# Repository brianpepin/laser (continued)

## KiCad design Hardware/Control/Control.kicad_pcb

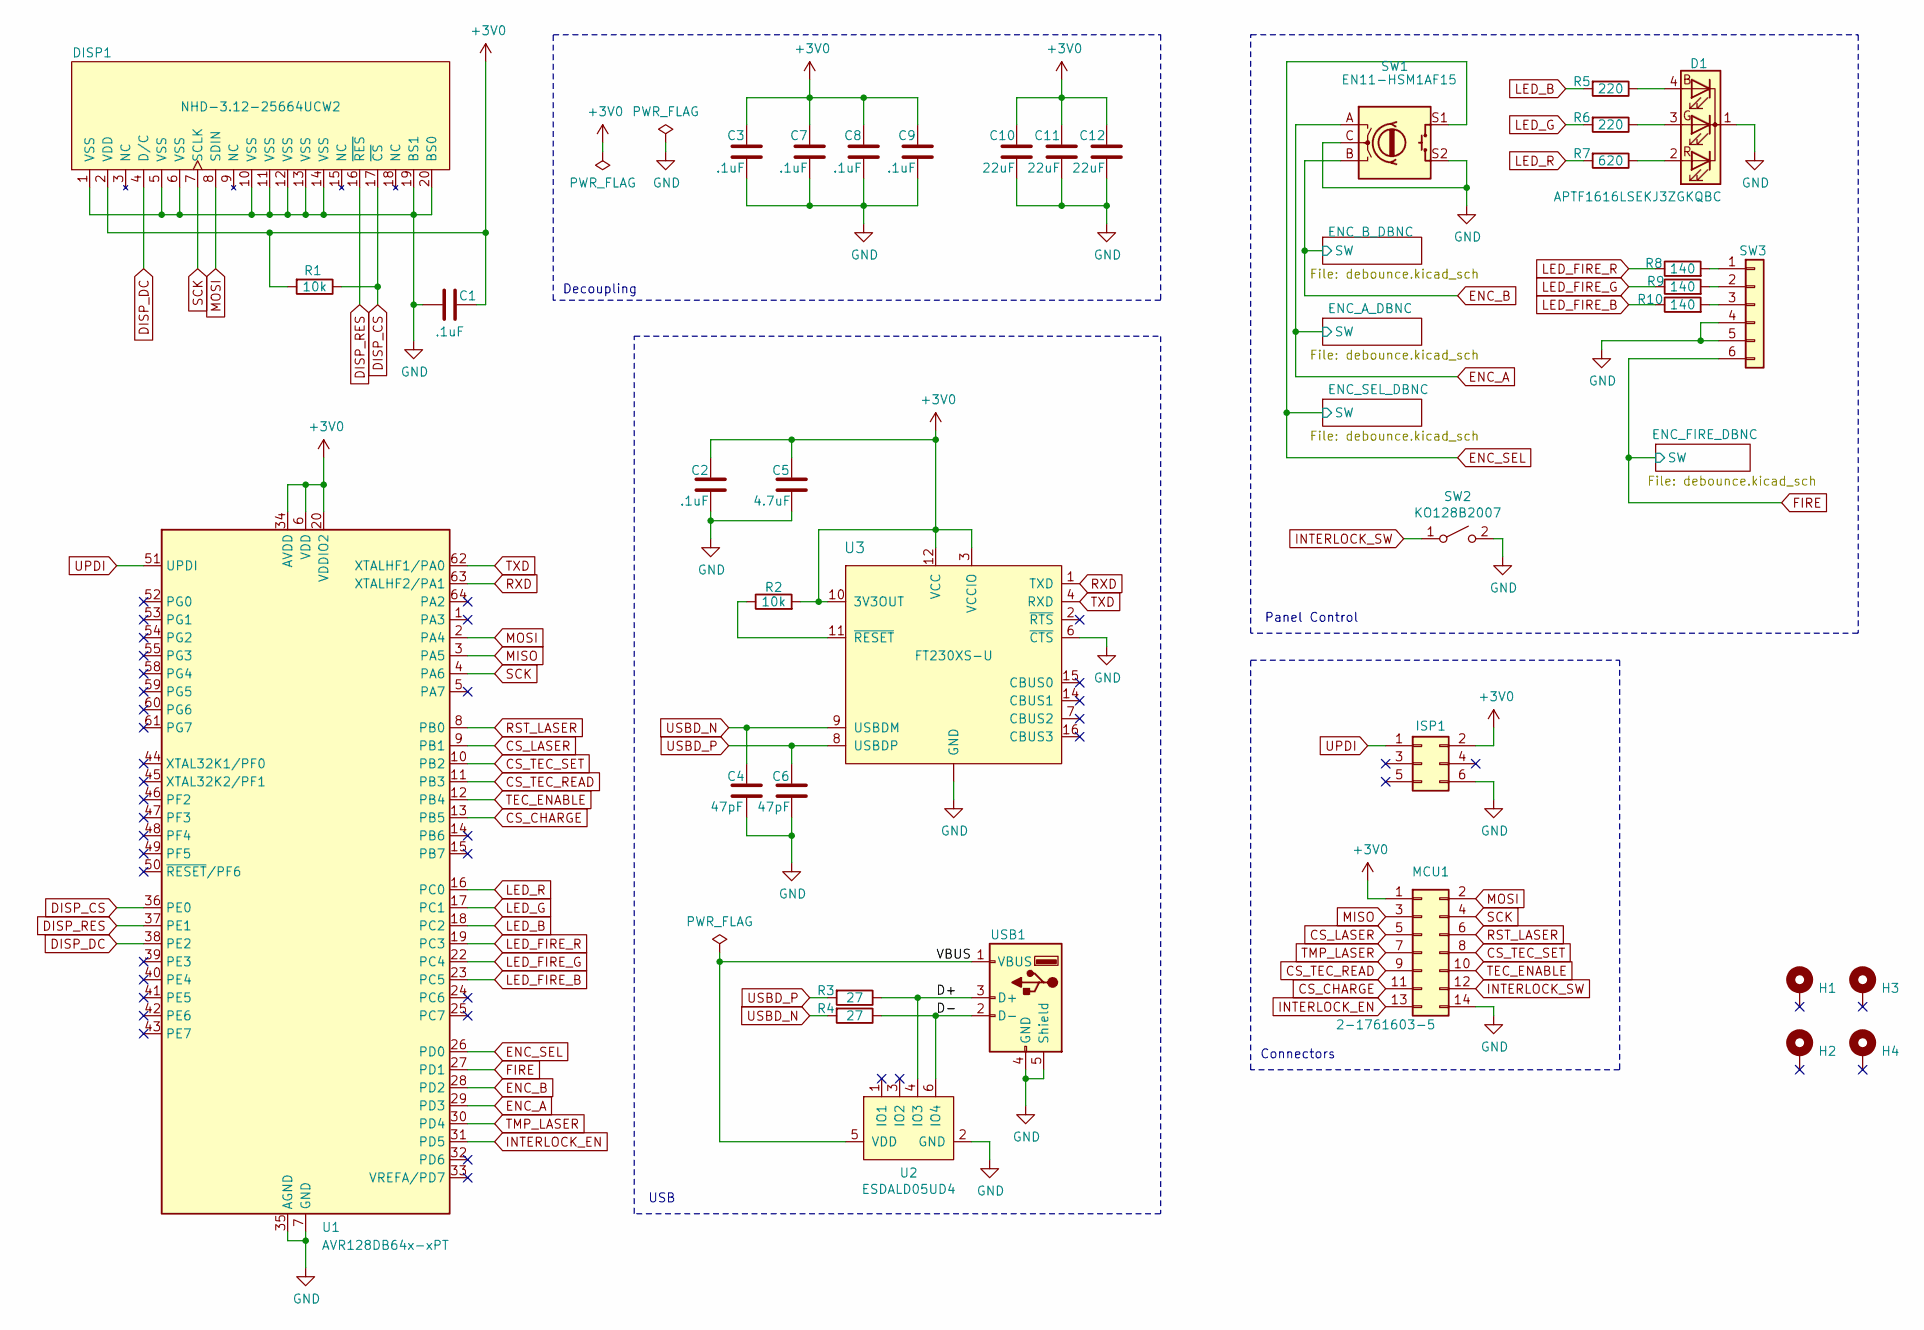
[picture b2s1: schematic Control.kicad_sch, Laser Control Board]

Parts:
C1, C2, C3, C7, C8, C9: .1uF; C_0805_2012Metric
C4, C6: 47pF; C_0805_2012Metric
C5: 4.7uF; C_0805_2012Metric
C10, C11, C12: 22uF; C_1206_3216Metric
D1: APTF1616LSEKJ3ZGKQBC; LED_Kingbright_KRGB_1.6x1.6mm
DISP1: NHD-3.12-25664UCW2; NHD-3.12-25664UC
H1, H2, H3, H4: MountingHole_Pad; MountingHole_3mm_Pad_Via
ISP1: 61200621621; IDC-Header_2x03_P2.54mm_Vertical
MCU1: 2-1761603-5; IDC-Header_2x07_P2.54mm_Vertical
R1, R2: 10k; R_0805_2012Metric
R3, R4: 27; R_0805_2012Metric
R5, R6: 220; R_0805_2012Metric
R7: 620; R_0805_2012Metric
R8, R9, R10: 140; R_0805_2012Metric
SW1: EN11-HSM1AF15; EN11-HSM
SW2: KO128B2007; PinHeader_1x02_P2.54mm_Vertical
SW3: Conn_01x06; PinHeader_1x06_P2.54mm_Vertical
U1: AVR128DB64x-xPT; TQFP-64_10x10mm_P0.5mm
U2: ESDALD05UD4; SOT-23-6
U3: FT230XS-U; SSOP-16_3.9x4.9mm_P0.635mm
USB1: UJ2-A-HR-G-TH; USB-A1HSW6

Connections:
+3V0: C1.2, C2.1, C3.2, C5.1, C7.2, C8.2, C9.2, C10.1, C11.1, C12.1, DISP1.2 (VDD), ISP1.2, MCU1.1, R1.2, R2.2, U1.6 (VDD), U1.20 (VDDIO2), U1.34 (AVDD), U1.56 (VDD), U3.3 (VCCIO), U3.10 (3V3OUT), U3.12 (VCC); also elsewhere on the board
/D+: R3.1, U2.4 (IO3), USB1.3 (D+)
/D-: R4.1, U2.6 (IO4), USB1.2 (D-)
/VBUS: U2.5 (VDD), USB1.1 (VBUS)
CS_CHARGE: MCU1.11, U1.13 (PB5)
CS_LASER: MCU1.5, U1.9 (PB1)
CS_TEC_READ: MCU1.9, U1.11 (PB3)
CS_TEC_SET: MCU1.8, U1.10 (PB2)
DISP_CS: DISP1.17 (~CS), R1.1, U1.36 (PE0)
DISP_DC: DISP1.4 (D/C), U1.38 (PE2)
DISP_RES: DISP1.16 (~RES), U1.37 (PE1)
ENC_A: SW1.A, U1.29 (PD3); also elsewhere on the board
ENC_B: SW1.B, U1.28 (PD2); also elsewhere on the board
ENC_SEL: SW1.S1, U1.26 (PD0); also elsewhere on the board
FIRE: SW3.6, U1.27 (PD1); also elsewhere on the board
GND: C1.1, C2.2, C3.1, C4.2, C5.2, C6.2, C7.1, C8.1, C9.1, C10.2, C11.2, C12.2, D1.1 (K), DISP1.1 (VSS), DISP1.5 (VSS), DISP1.6 (VSS), DISP1.10 (VSS), DISP1.11 (VSS), DISP1.12 (VSS), DISP1.13 (VSS), DISP1.14 (VSS), DISP1.19 (BS1), DISP1.20 (BS0), ISP1.6, MCU1.14, SW1.C, SW1.S2, SW2.2 (B), SW3.4, SW3.5, U1.7 (GND), U1.21 (GND), U1.35 (AGND), U1.57 (GND), U2.2 (GND), U3.5 (GND), U3.6 (~CTS), U3.13 (GND), USB1.4 (GND), USB1.5 (Shield); also elsewhere on the board
INTERLOCK_EN: MCU1.13, U1.31 (PD5)
INTERLOCK_SW: MCU1.12, SW2.1 (A)
LED_B: R5.2, U1.18 (PC2)
LED_FIRE_B: R10.1, U1.23 (PC5)
LED_FIRE_G: R9.1, U1.22 (PC4)
LED_FIRE_R: R8.1, U1.19 (PC3)
LED_G: R6.2, U1.17 (PC1)
LED_R: R7.2, U1.16 (PC0)
MISO: MCU1.3, U1.3 (PA5)
MOSI: DISP1.8 (SDIN), MCU1.2, U1.2 (PA4)
unnamed: D1.4 (BA), R5.1
unnamed: D1.3 (GA), R6.1
unnamed: D1.2 (RA), R7.1
unnamed: R8.2, SW3.1
unnamed: R9.2, SW3.2
unnamed: R10.2, SW3.3
unnamed: R2.1, U3.11 (~RESET)
RST_LASER: MCU1.6, U1.8 (PB0)
RXD: U1.63 (XTALHF2/PA1), U3.1 (TXD)
SCK: DISP1.7 (SCLK), MCU1.4, U1.4 (PA6)
TEC_ENABLE: MCU1.10, U1.12 (PB4)
TMP_LASER: MCU1.7, U1.30 (PD4)
TXD: U1.62 (XTALHF1/PA0), U3.4 (RXD)
UPDI: ISP1.1, U1.51 (UPDI)
USBD_N: C4.1, R4.2, U3.9 (USBDM)
USBD_P: C6.1, R3.2, U3.8 (USBDP)

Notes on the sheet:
USB
Connectors
Panel Control
Decoupling

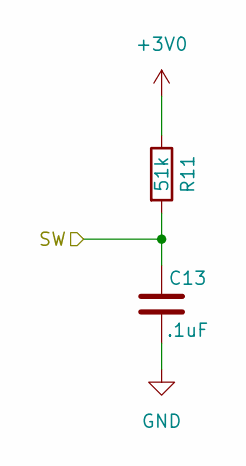
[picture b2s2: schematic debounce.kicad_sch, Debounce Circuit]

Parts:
C13: .1uF; C_0805_2012Metric
R11: 51k; R_0805_2012Metric

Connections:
+3V0: R11.1; also elsewhere on the board
ENC_B: C13.1, R11.2; also elsewhere on the board
GND: C13.2; also elsewhere on the board

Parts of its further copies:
C14, C15, C16: .1uF; C_0805_2012Metric
R12, R13, R14: 51k; R_0805_2012Metric

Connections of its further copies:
+3V0: R12.1, R13.1, R14.1; also elsewhere on the board
ENC_A: C14.1, R12.2; also elsewhere on the board
ENC_SEL: C15.1, R13.2; also elsewhere on the board
FIRE: C16.1, R14.2; also elsewhere on the board
GND: C14.2, C15.2, C16.2; also elsewhere on the board

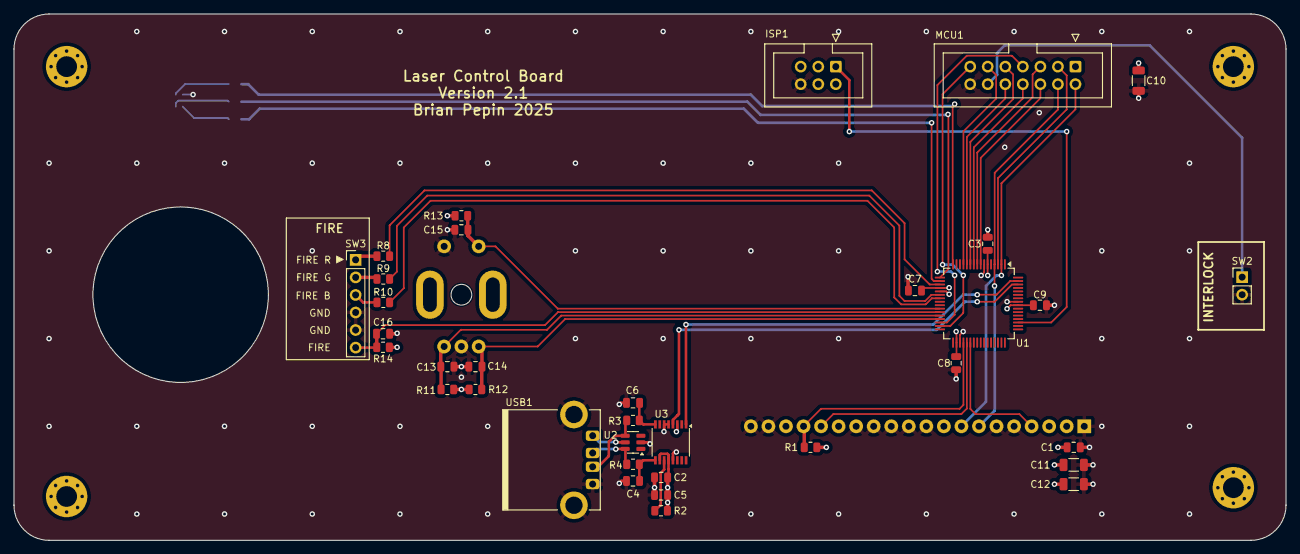
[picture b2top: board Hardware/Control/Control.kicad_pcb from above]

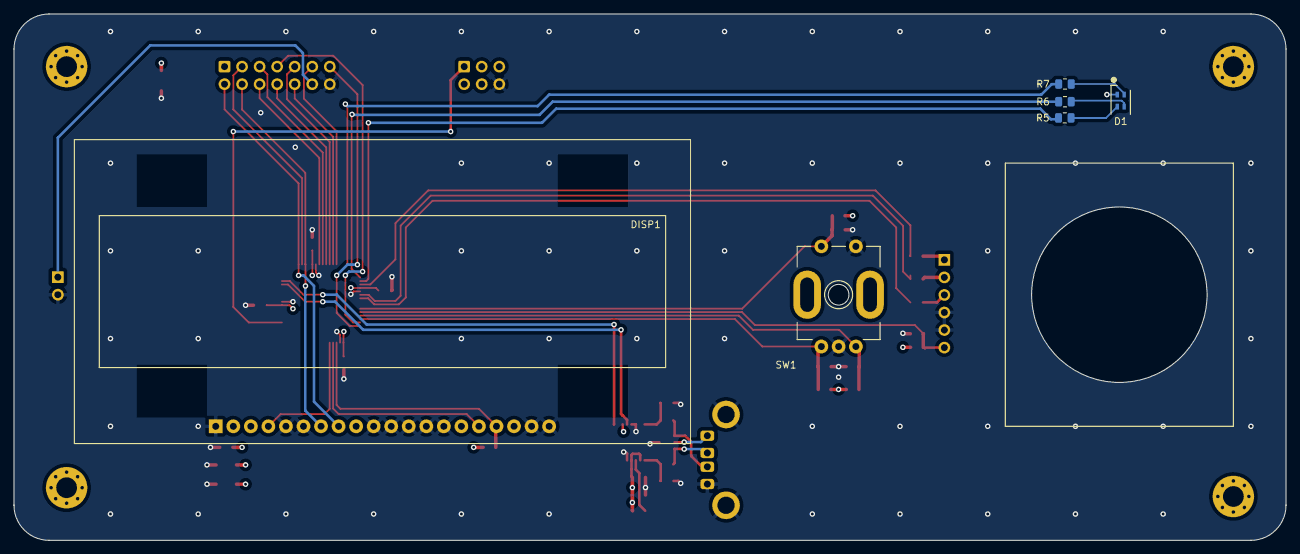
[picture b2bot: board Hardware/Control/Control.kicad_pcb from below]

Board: 4 copper layers, 184.2 x 76.2 mm, 45 parts (6 on the bottom side), 42 nets.

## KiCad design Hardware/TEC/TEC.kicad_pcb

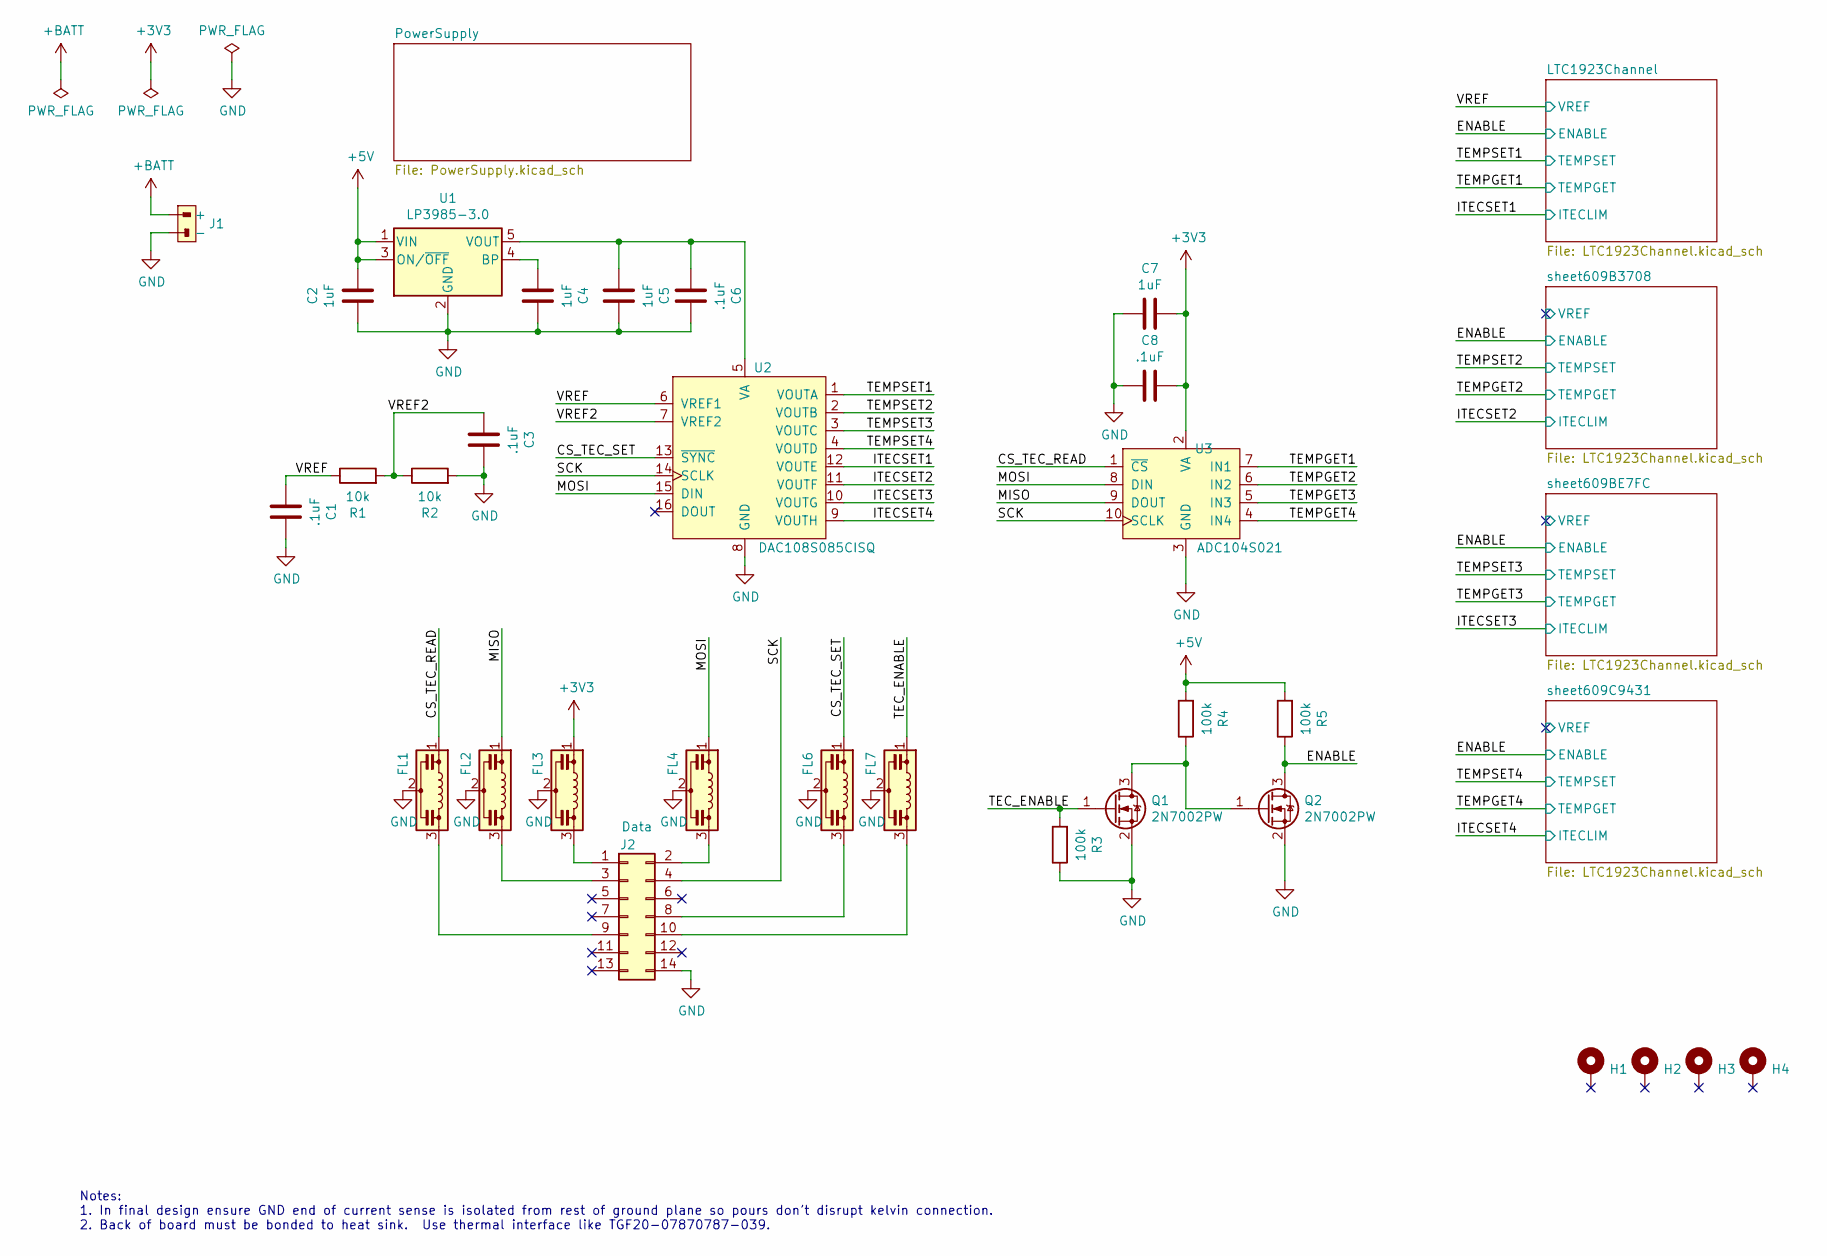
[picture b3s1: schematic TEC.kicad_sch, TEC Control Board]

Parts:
C1, C3, C6, C8: .1uF; C_0805_2012Metric; PartNo VJ0805Y104KXXAT
C2, C4, C5, C7: 1uF; C_0805_2012Metric; PartNo UMF212B7105KGHT
FL1, FL2, FL3, FL4, FL6, FL7: NFL21SP206X1C7D; EMI_805; PartNo NFL21SP206X1C7D
H1, H2, H3, H4: MountingHole_Pad; MountingHole_3mm_Pad_Via
J1: DEANS; Connector_Deans_Male
J2: Data; IDC-Header_2x07_P2.54mm_Horizontal; PartNo 2-1761605-5
Q1, Q2: 2N7002PW; SOT-23; PartNo 2N7002PW,115
R1, R2: 10k; R_0805_2012Metric; PartNo AC0805FR-0710KL
R3, R4, R5: 100k; R_0805_2012Metric; PartNo RC0805FR-07100KL
U1: LP3985-3.0; SOT-23-5; PartNo LP3985IM5X-3.0/NOPB
U2: DAC108S085CISQ; WQFN-16-1EP_4x4mm_P0.5mm_EP2.6x2.6mm_ThermalVias; PartNo DAC108S085CISQ/NOPB
U3: ADC104S021; VSSOP-10_3x3mm_P0.5mm; PartNo ADC104S021CIMMX/NOPB

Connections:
+3V3: C7.1, C8.1, FL3.1, U3.2 (VA)
+5V: C2.1, R4.2, R5.2, U1.1 (VIN), U1.3 (ON/~OFF); also elsewhere on the board
+BATT: J1.+; also elsewhere on the board
/CS_TEC_READ: FL1.1, U3.1 (~CS)
/CS_TEC_SET: FL6.1, U2.13 (~SYNC)
/ENABLE: Q2.3 (D), R5.1; also elsewhere on the board
/ITECSET1: U2.12 (VOUTE); also elsewhere on the board
/ITECSET2: U2.11 (VOUTF); also elsewhere on the board
/ITECSET3: U2.10 (VOUTG); also elsewhere on the board
/ITECSET4: U2.9 (VOUTH); also elsewhere on the board
/MISO: FL2.1, U3.9 (DOUT)
/MOSI: FL4.1, U2.15 (DIN), U3.8 (DIN)
/SCK: J2.4, U2.14 (SCLK), U3.10 (SCLK)
/TEC_ENABLE: FL7.1, Q1.1 (G), R3.2
/TEMPGET1: U3.7 (IN1); also elsewhere on the board
/TEMPGET2: U3.6 (IN2); also elsewhere on the board
/TEMPGET3: U3.5 (IN3); also elsewhere on the board
/TEMPGET4: U3.4 (IN4); also elsewhere on the board
/TEMPSET1: U2.1 (VOUTA); also elsewhere on the board
/TEMPSET2: U2.2 (VOUTB); also elsewhere on the board
/TEMPSET3: U2.3 (VOUTC); also elsewhere on the board
/TEMPSET4: U2.4 (VOUTD); also elsewhere on the board
/VREF: C1.2, R1.1, U2.6 (VREF1); also elsewhere on the board
/VREF2: C3.2, R1.2, R2.1, U2.7 (VREF2)
GND: C1.1, C2.2, C3.1, C4.1, C5.1, C6.1, C7.2, C8.2, FL1.2, FL2.2, FL3.2, FL4.2, FL6.2, FL7.2, J1.-, J2.14, Q1.2 (S), Q2.2 (S), R2.2, R3.1, U1.2 (GND), U2.8 (GND), U2.17 (GND), U3.3 (GND); also elsewhere on the board
unnamed: FL3.3, J2.1
unnamed: FL4.3, J2.2
unnamed: FL2.3, J2.3
unnamed: FL6.3, J2.8
unnamed: FL1.3, J2.9
unnamed: FL7.3, J2.10
unnamed: Q1.3 (D), Q2.1 (G), R4.1
unnamed: C4.2, U1.4 (BP)
unnamed: C5.2, C6.2, U1.5 (VOUT), U2.5 (VA)

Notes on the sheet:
Notes: 1. In final design ensure GND end of current sense is isolated from rest of ground plane so pours don’t disrupt kelvin connection. 2. Back of board must be bonded to heat sink. Use thermal interface like TGF20-07870787-039.

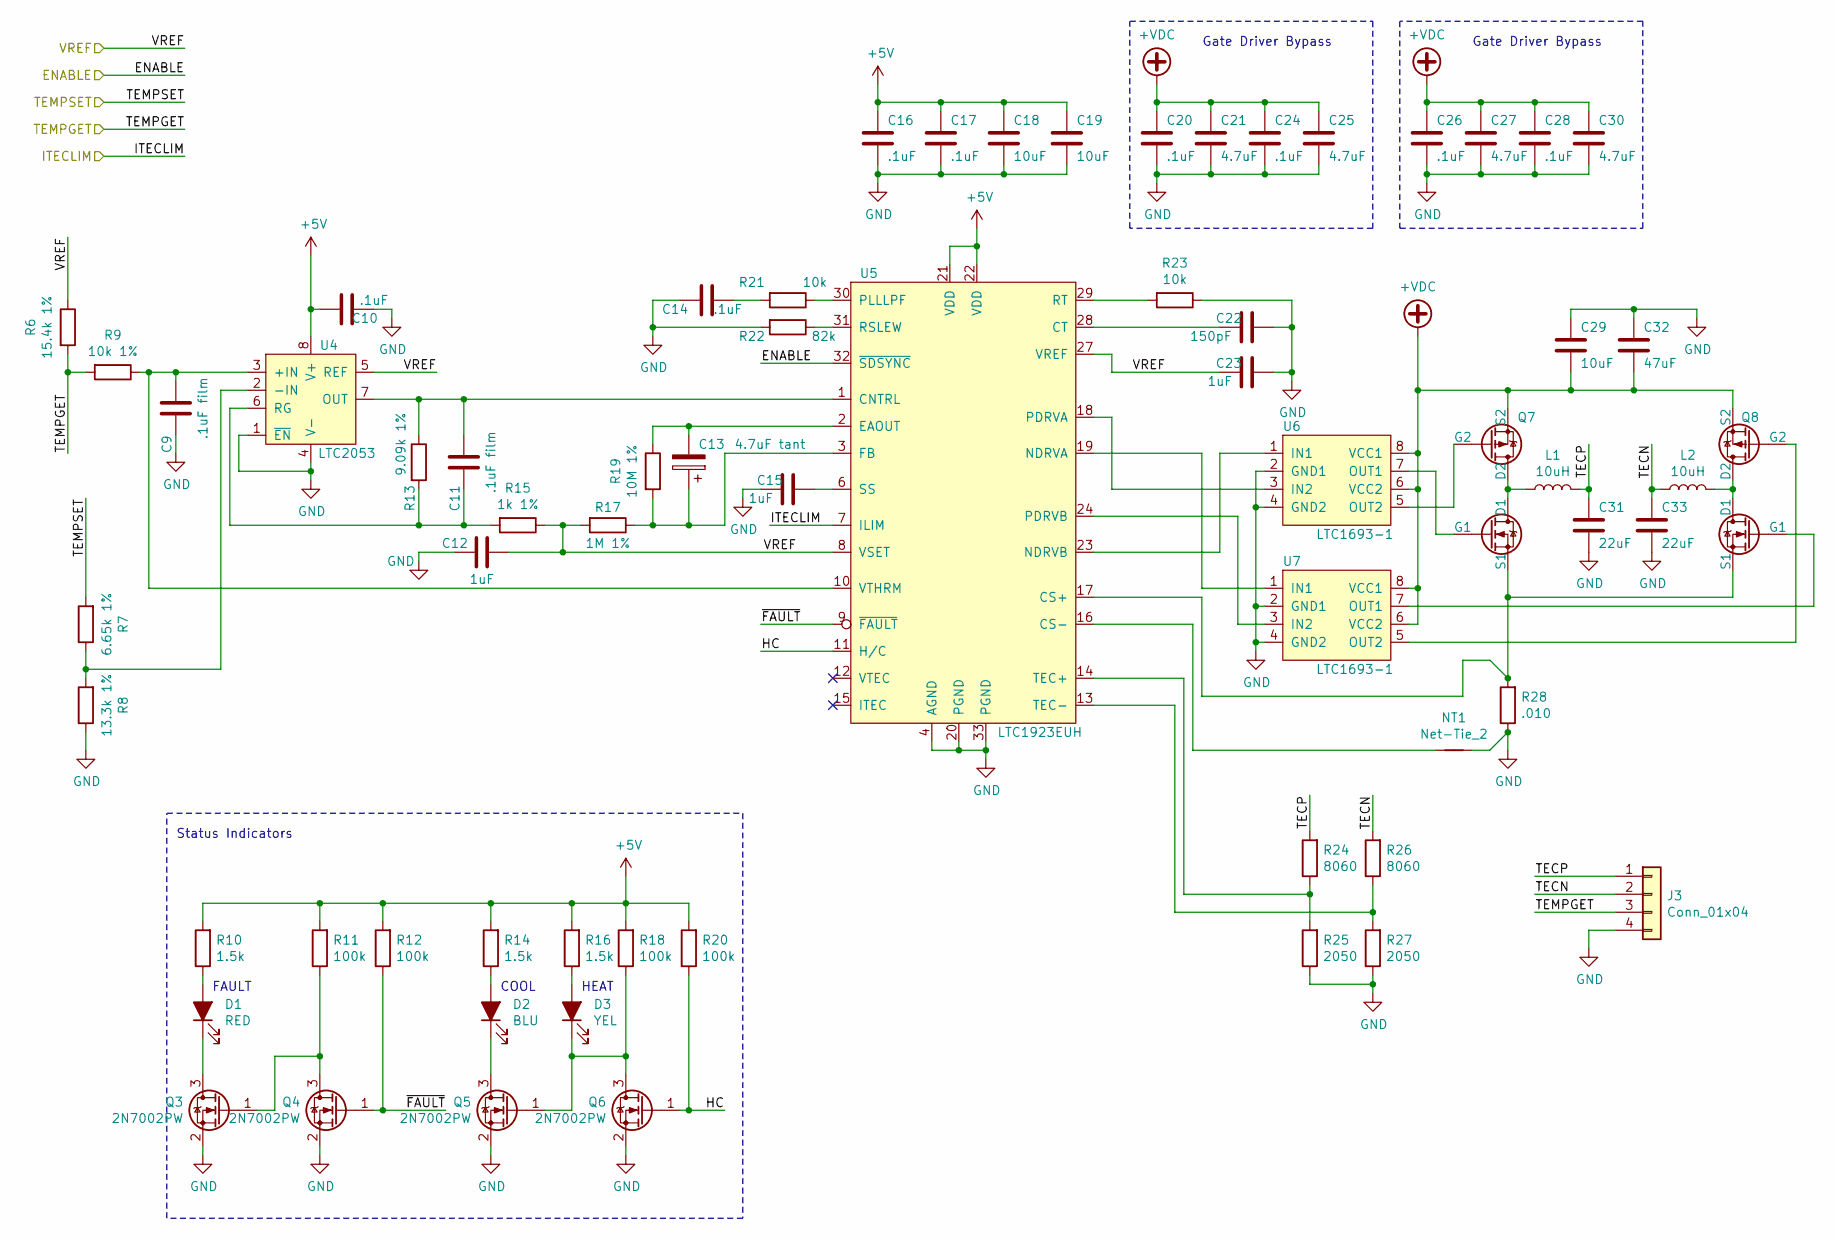
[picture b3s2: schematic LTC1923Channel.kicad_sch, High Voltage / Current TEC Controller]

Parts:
C9, C11: .1uF film; C_0805_2012Metric; PartNo FCA0805C104M-J2
C10, C14, C16, C17, C20, C24, C26, C28: .1uF; C_0805_2012Metric; PartNo VJ0805Y104KXXAT
C12, C15, C23: 1uF; C_0805_2012Metric; PartNo UMF212B7105KGHT
C13: 4.7uF tant; C_0805_2012Metric; PartNo T529P475M025AAE300
C18, C19, C29: 10uF; C_0805_2012Metric; PartNo C2012X7S1E106K125AE
C21, C25, C27, C30: 4.7uF; C_0805_2012Metric; PartNo C0805C475K3RACTU
C22: 150pF; C_0805_2012Metric; PartNo C0805C151J5GACTU
C31, C33: 22uF; C_1206_3216Metric; PartNo 12063D226MAT2A
C32: 47uF; C_1206_3216Metric; PartNo C3216X5R1E476M160AC
D1: RED; LED_0805_2012Metric; PartNo APT2012LSECK/J3-PRV
D2: BLU; LED_0805_2012Metric; PartNo 5973605607F
D3: YEL; LED_0805_2012Metric; PartNo SM0805YCL
J3: Conn_01x04; Molex_Nano-Fit_105313-xx04_1x04_P2.50mm_Horizontal; PartNo 105313-1304
L1, L2: 10uH; L_Pulse_PA4343_2; PartNo PA4343.103ANLT
NT1: Net-Tie_2; NetTie-2_SMD_Pad0.5mm
Q3, Q4, Q5, Q6: 2N7002PW; SOT-23; PartNo 2N7002PW,115
Q7, Q8: SQJ504EP; PowerPAK_SO-8_Dual; PartNo SQJ504EP-T1_GE3
R6: 15.4k 1%; R_0805_2012Metric; PartNo ERJ-6ENF1542V
R7: 6.65k 1%; R_0805_2012Metric; PartNo ERJ-6ENF6651V
R8: 13.3k 1%; R_0805_2012Metric; PartNo CRCW080513K3FKEA
R9: 10k 1%; R_0805_2012Metric; PartNo AC0805FR-0710KL
R10, R14, R16: 1.5k; R_0805_2012Metric; PartNo CR0805-FX-1501ELF
R11, R12, R18, R20: 100k; R_0805_2012Metric; PartNo RC0805FR-07100KL
R13: 9.09k 1%; R_0805_2012Metric; PartNo ERJ-6ENF9091V
R15: 1k 1%; R_0805_2012Metric; PartNo RC0805FR-071KL
R17: 1M 1%; R_0805_2012Metric; PartNo RK73H2ARTTD1004F
R19: 10M 1%; R_0805_2012Metric; PartNo CRCW080510M0FKEAC
R21, R23: 10k; R_0805_2012Metric; PartNo AC0805FR-0710KL
R22: 82k; R_0805_2012Metric; PartNo ERJ-6ENF8202V
R24, R26: 8060; R_0805_2012Metric; PartNo CR0805-FX-8061ELF
R25, R27: 2050; R_0805_2012Metric; PartNo CR0805-FX-2051ELF
R28: .010; R_2010_5025Metric; PartNo TLR2HWDTE10L0F75
U4: LTC2053; MSOP-8_3x3mm_P0.65mm; PartNo LTC2053IMS8#PBF
U5: LTC1923EUH; QFN-32-1EP_5x5mm_P0.5mm_EP3.45x3.45mm_ThermalVias; PartNo LTC1923EUH#PBF
U6, U7: LTC1693-1; SO-8_3.9x4.9mm_P1.27mm; PartNo LTC1693-1IS8#PBF

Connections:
+5V: C10.2, C16.2, C17.2, C18.2, C19.2, R10.2, R11.2, R12.2, R14.2, R16.2, R18.2, R20.2, U4.8 (V+), U5.21 (VDD), U5.22 (VDD); also elsewhere on the board
+VDC: C20.2, C21.2, C24.2, C25.2, C26.2, C27.2, C28.2, C29.1, C30.2, C32.1, Q7.3 (S2), Q8.3 (S2), U6.6 (VCC2), U6.8 (VCC1), U7.6 (VCC2), U7.8 (VCC1); also elsewhere on the board
/ENABLE: U5.32 (~SDSYNC); also elsewhere on the board
/ITECSET1: U5.7 (ILIM); also elsewhere on the board
/LTC1923Channel/HC: Q6.1 (G), R20.1, U5.11 (H/C)
/LTC1923Channel/TECN: C33.2, J3.2, L2.1, R26.2
/LTC1923Channel/TECP: C31.2, J3.1, L1.2, R24.2
/LTC1923Channel/~FAULT: Q4.1 (G), R12.1, U5.9 (~FAULT)
/TEMPGET1: J3.3, R6.2, R9.2; also elsewhere on the board
/TEMPSET1: R7.2; also elsewhere on the board
/VREF: C12.1, C23.1, R6.1, R15.1, R17.2, U4.5 (REF), U5.8 (VSET), U5.27 (VREF); also elsewhere on the board
GND: C9.2, C10.1, C12.2, C14.2, C15.1, C16.1, C17.1, C18.1, C19.1, C20.1, C21.1, C22.2, C23.2, C24.1, C25.1, C26.1, C27.1, C28.1, C29.2, C30.1, C31.1, C32.2, C33.1, J3.4, NT1.2, Q3.2 (S), Q4.2 (S), Q5.2 (S), Q6.2 (S), R8.1, R22.2, R23.1, R25.1, R27.1, R28.1, U4.1 (~EN), U4.4 (V-), U5.4 (AGND), U5.20 (PGND), U5.33 (PGND), U6.2 (GND1), U6.4 (GND2), U7.2 (GND1), U7.4 (GND2); also elsewhere on the board
unnamed: C14.1, R21.2
unnamed: D1.2 (A), R10.1
unnamed: D1.1 (K), Q3.3 (D)
unnamed: D2.2 (A), R14.1
unnamed: D2.1 (K), Q5.3 (D)
unnamed: D3.2 (A), R16.1
unnamed: D3.1 (K), Q5.1 (G), Q6.3 (D), R18.1
unnamed: Q3.1 (G), Q4.3 (D), R11.1
unnamed: L1.1, Q7.5 (D1), Q7.6 (D2)
unnamed: Q7.2 (G1), U6.7 (OUT1)
unnamed: Q7.4 (G2), U6.5 (OUT2)
unnamed: Q7.1 (S1), Q8.1 (S1), R28.2, U5.17 (CS+)
unnamed: L2.2, Q8.5 (D1), Q8.6 (D2)
unnamed: Q8.2 (G1), U7.7 (OUT1)
unnamed: Q8.4 (G2), U7.5 (OUT2)
unnamed: C9.1, R9.1, U4.3 (+IN), U5.10 (VTHRM)
unnamed: R7.1, R8.2, U4.2 (-IN)
unnamed: C11.1, R13.1, U4.7 (OUT), U5.1 (CNTRL)
unnamed: C11.2, R13.2, R15.2, U4.6 (RG)
unnamed: NT1.1, U5.16 (CS-)
unnamed: C22.1, U5.28 (CT)
unnamed: C13.2, R19.1, U5.2 (EAOUT)
unnamed: C13.1, R17.1, R19.2, U5.3 (FB)
unnamed: U5.19 (NDRVA), U7.1 (IN1)
unnamed: U5.23 (NDRVB), U6.1 (IN1)
unnamed: U5.18 (PDRVA), U6.3 (IN2)
unnamed: U5.24 (PDRVB), U7.3 (IN2)
unnamed: R21.1, U5.30 (PLLLPF)
unnamed: R22.1, U5.31 (RSLEW)
unnamed: R23.2, U5.29 (RT)
unnamed: C15.2, U5.6 (SS)
unnamed: R24.1, R25.2, U5.14 (TEC+)
unnamed: R26.1, R27.2, U5.13 (TEC-)

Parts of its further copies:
C36, C38, C61, C63, C86, C88: .1uF film; C_0805_2012Metric; PartNo FCA0805C104M-J2
C37, C41, C43, C44, C47, C51, C53, C55, C62, C66, C68, C69, C72, C76, C78, C80, C87, C91, C93, C94, C97, C101, C103, C105: .1uF; C_0805_2012Metric; PartNo VJ0805Y104KXXAT
C39, C42, C50, C64, C67, C75, C89, C92, C100: 1uF; C_0805_2012Metric; PartNo UMF212B7105KGHT
C40, C65, C90: 4.7uF tant; C_0805_2012Metric; PartNo T529P475M025AAE300
C45, C46, C56, C70, C71, C81, C95, C96, C106: 10uF; C_0805_2012Metric; PartNo C2012X7S1E106K125AE
C48, C52, C54, C57, C73, C77, C79, C82, C98, C102, C104, C107: 4.7uF; C_0805_2012Metric; PartNo C0805C475K3RACTU
C49, C74, C99: 150pF; C_0805_2012Metric; PartNo C0805C151J5GACTU
C58, C60, C83, C85, C108, C110: 22uF; C_1206_3216Metric; PartNo 12063D226MAT2A
C59, C84, C109: 47uF; C_1206_3216Metric; PartNo C3216X5R1E476M160AC
D4, D7, D10: RED; LED_0805_2012Metric; PartNo APT2012LSECK/J3-PRV
D5, D8, D11: BLU; LED_0805_2012Metric; PartNo 5973605607F
D6, D9, D12: YEL; LED_0805_2012Metric; PartNo SM0805YCL
J4, J5, J6: Conn_01x04; Molex_Nano-Fit_105313-xx04_1x04_P2.50mm_Horizontal; PartNo 105313-1304
L3, L4, L5, L6, L7, L8: 10uH; L_Pulse_PA4343_2; PartNo PA4343.103ANLT
NT2, NT3, NT4: Net-Tie_2; NetTie-2_SMD_Pad0.5mm
Q12, Q13, Q14, Q15, Q18, Q19, Q20, Q21, Q24, Q25, Q26, Q27: 2N7002PW; SOT-23; PartNo 2N7002PW,115
Q16, Q17, Q22, Q23, Q28, Q29: SQJ504EP; PowerPAK_SO-8_Dual; PartNo SQJ504EP-T1_GE3
R31, R54, R77: 15.4k 1%; R_0805_2012Metric; PartNo ERJ-6ENF1542V
R32, R55, R78: 6.65k 1%; R_0805_2012Metric; PartNo ERJ-6ENF6651V
R33, R56, R79: 13.3k 1%; R_0805_2012Metric; PartNo CRCW080513K3FKEA
R34, R57, R80: 10k 1%; R_0805_2012Metric; PartNo AC0805FR-0710KL
R35, R39, R41, R58, R62, R64, R81, R85, R87: 1.5k; R_0805_2012Metric; PartNo CR0805-FX-1501ELF
R36, R37, R43, R45, R59, R60, R66, R68, R82, R83, R89, R91: 100k; R_0805_2012Metric; PartNo RC0805FR-07100KL
R38, R61, R84: 9.09k 1%; R_0805_2012Metric; PartNo ERJ-6ENF9091V
R40, R63, R86: 1k 1%; R_0805_2012Metric; PartNo RC0805FR-071KL
R42, R65, R88: 1M 1%; R_0805_2012Metric; PartNo RK73H2ARTTD1004F
R44, R67, R90: 10M 1%; R_0805_2012Metric; PartNo CRCW080510M0FKEAC
R46, R48, R69, R71, R92, R94: 10k; R_0805_2012Metric; PartNo AC0805FR-0710KL
R47, R70, R93: 82k; R_0805_2012Metric; PartNo ERJ-6ENF8202V
R49, R51, R72, R74, R95, R97: 8060; R_0805_2012Metric; PartNo CR0805-FX-8061ELF
R50, R52, R73, R75, R96, R98: 2050; R_0805_2012Metric; PartNo CR0805-FX-2051ELF
R53, R76, R99: .010; R_2010_5025Metric; PartNo TLR2HWDTE10L0F75
U9, U13, U17: LTC2053; MSOP-8_3x3mm_P0.65mm; PartNo LTC2053IMS8#PBF
U10, U14, U18: LTC1923EUH; QFN-32-1EP_5x5mm_P0.5mm_EP3.45x3.45mm_ThermalVias; PartNo LTC1923EUH#PBF
U11, U12, U15, U16, U19, U20: LTC1693-1; SO-8_3.9x4.9mm_P1.27mm; PartNo LTC1693-1IS8#PBF

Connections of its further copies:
+5V: C37.2, C43.2, C44.2, C45.2, C46.2, C62.2, C68.2, C69.2, C70.2, C71.2, C87.2, C93.2, C94.2, C95.2, C96.2, R35.2, R36.2, R37.2, R39.2, R41.2, R43.2, R45.2, R58.2, R59.2, R60.2, R62.2, R64.2, R66.2, R68.2, R81.2, R82.2, R83.2, R85.2, R87.2, R89.2, R91.2, U9.8 (V+), U10.21 (VDD), U10.22 (VDD), U13.8 (V+), U14.21 (VDD), U14.22 (VDD), U17.8 (V+), U18.21 (VDD), U18.22 (VDD); also elsewhere on the board
+VDC: C47.2, C48.2, C51.2, C52.2, C53.2, C54.2, C55.2, C56.1, C57.2, C59.1, C72.2, C73.2, C76.2, C77.2, C78.2, C79.2, C80.2, C81.1, C82.2, C84.1, C97.2, C98.2, C101.2, C102.2, C103.2, C104.2, C105.2, C106.1, C107.2, C109.1, Q16.3 (S2), Q17.3 (S2), Q22.3 (S2), Q23.3 (S2), Q28.3 (S2), Q29.3 (S2), U11.6 (VCC2), U11.8 (VCC1), U12.6 (VCC2), U12.8 (VCC1), U15.6 (VCC2), U15.8 (VCC1), U16.6 (VCC2), U16.8 (VCC1), U19.6 (VCC2), U19.8 (VCC1), U20.6 (VCC2), U20.8 (VCC1); also elsewhere on the board
/ENABLE: U10.32 (~SDSYNC), U14.32 (~SDSYNC), U18.32 (~SDSYNC); also elsewhere on the board
/ITECSET2: U10.7 (ILIM); also elsewhere on the board
/ITECSET3: U14.7 (ILIM); also elsewhere on the board
/ITECSET4: U18.7 (ILIM); also elsewhere on the board
/TEMPGET2: J4.3, R31.2, R34.2; also elsewhere on the board
/TEMPGET3: J5.3, R54.2, R57.2; also elsewhere on the board
/TEMPGET4: J6.3, R77.2, R80.2; also elsewhere on the board
/TEMPSET2: R32.2; also elsewhere on the board
/TEMPSET3: R55.2; also elsewhere on the board
/TEMPSET4: R78.2; also elsewhere on the board
/sheet609B3708/HC: Q15.1 (G), R45.1, U10.11 (H/C)
/sheet609B3708/TECN: C60.2, J4.2, L4.1, R51.2
/sheet609B3708/TECP: C58.2, J4.1, L3.2, R49.2
/sheet609B3708/VREF: C39.1, C50.1, R31.1, R40.1, R42.2, U9.5 (REF), U10.8 (VSET), U10.27 (VREF)
/sheet609B3708/~FAULT: Q13.1 (G), R37.1, U10.9 (~FAULT)
/sheet609BE7FC/HC: Q21.1 (G), R68.1, U14.11 (H/C)
/sheet609BE7FC/TECN: C85.2, J5.2, L6.1, R74.2
/sheet609BE7FC/TECP: C83.2, J5.1, L5.2, R72.2
/sheet609BE7FC/VREF: C64.1, C75.1, R54.1, R63.1, R65.2, U13.5 (REF), U14.8 (VSET), U14.27 (VREF)
/sheet609BE7FC/~FAULT: Q19.1 (G), R60.1, U14.9 (~FAULT)
/sheet609C9431/HC: Q27.1 (G), R91.1, U18.11 (H/C)
/sheet609C9431/TECN: C110.2, J6.2, L8.1, R97.2
/sheet609C9431/TECP: C108.2, J6.1, L7.2, R95.2
/sheet609C9431/VREF: C89.1, C100.1, R77.1, R86.1, R88.2, U17.5 (REF), U18.8 (VSET), U18.27 (VREF)
/sheet609C9431/~FAULT: Q25.1 (G), R83.1, U18.9 (~FAULT)
GND: C36.2, C37.1, C39.2, C41.2, C42.1, C43.1, C44.1, C45.1, C46.1, C47.1, C48.1, C49.2, C50.2, C51.1, C52.1, C53.1, C54.1, C55.1, C56.2, C57.1, C58.1, C59.2, C60.1, C61.2, C62.1, C64.2, C66.2, C67.1, C68.1, C69.1, C70.1, C71.1, C72.1, C73.1, C74.2, C75.2, C76.1, C77.1, C78.1, C79.1, C80.1, C81.2, C82.1, C83.1, C84.2, C85.1, C86.2, C87.1, C89.2, C91.2, C92.1, C93.1, C94.1, C95.1, C96.1, C97.1, C98.1, C99.2, C100.2, C101.1, C102.1, C103.1, C104.1, C105.1, C106.2, C107.1, C108.1, C109.2, C110.1, J4.4, J5.4, J6.4, NT2.2, NT3.2, NT4.2, Q12.2 (S), Q13.2 (S), Q14.2 (S), Q15.2 (S), Q18.2 (S), Q19.2 (S), Q20.2 (S), Q21.2 (S), Q24.2 (S), Q25.2 (S), Q26.2 (S), Q27.2 (S), R33.1, R47.2, R48.1, R50.1, R52.1, R53.1, R56.1, R70.2, R71.1, R73.1, R75.1, R76.1, R79.1, R93.2, R94.1, R96.1, R98.1, R99.1, U9.1 (~EN), U9.4 (V-), U10.4 (AGND), U10.20 (PGND), U10.33 (PGND), U11.2 (GND1), U11.4 (GND2), U12.2 (GND1), U12.4 (GND2), U13.1 (~EN), U13.4 (V-), U14.4 (AGND), U14.20 (PGND), U14.33 (PGND), U15.2 (GND1), U15.4 (GND2), U16.2 (GND1), U16.4 (GND2), U17.1 (~EN), U17.4 (V-), U18.4 (AGND), U18.20 (PGND), U18.33 (PGND), U19.2 (GND1), U19.4 (GND2), U20.2 (GND1), U20.4 (GND2); also elsewhere on the board
unnamed: C41.1, R46.2
unnamed: C66.1, R69.2
unnamed: C91.1, R92.2
unnamed: D4.2 (A), R35.1
unnamed: D4.1 (K), Q12.3 (D)
unnamed: D5.2 (A), R39.1
unnamed: D5.1 (K), Q14.3 (D)
unnamed: D6.2 (A), R41.1
unnamed: D6.1 (K), Q14.1 (G), Q15.3 (D), R43.1
unnamed: D7.2 (A), R58.1
unnamed: D7.1 (K), Q18.3 (D)
unnamed: D8.2 (A), R62.1
unnamed: D8.1 (K), Q20.3 (D)
unnamed: D9.2 (A), R64.1
unnamed: D9.1 (K), Q20.1 (G), Q21.3 (D), R66.1
unnamed: D10.2 (A), R81.1
unnamed: D10.1 (K), Q24.3 (D)
unnamed: D11.2 (A), R85.1
unnamed: D11.1 (K), Q26.3 (D)
unnamed: D12.2 (A), R87.1
unnamed: D12.1 (K), Q26.1 (G), Q27.3 (D), R89.1
unnamed: Q12.1 (G), Q13.3 (D), R36.1
unnamed: L3.1, Q16.5 (D1), Q16.6 (D2)
unnamed: Q16.2 (G1), U11.7 (OUT1)
unnamed: Q16.4 (G2), U11.5 (OUT2)
unnamed: Q16.1 (S1), Q17.1 (S1), R53.2, U10.17 (CS+)
unnamed: L4.2, Q17.5 (D1), Q17.6 (D2)
unnamed: Q17.2 (G1), U12.7 (OUT1)
unnamed: Q17.4 (G2), U12.5 (OUT2)
unnamed: Q18.1 (G), Q19.3 (D), R59.1
unnamed: L5.1, Q22.5 (D1), Q22.6 (D2)
unnamed: Q22.2 (G1), U15.7 (OUT1)
unnamed: Q22.4 (G2), U15.5 (OUT2)
unnamed: Q22.1 (S1), Q23.1 (S1), R76.2, U14.17 (CS+)
unnamed: L6.2, Q23.5 (D1), Q23.6 (D2)
unnamed: Q23.2 (G1), U16.7 (OUT1)
unnamed: Q23.4 (G2), U16.5 (OUT2)
unnamed: Q24.1 (G), Q25.3 (D), R82.1
unnamed: L7.1, Q28.5 (D1), Q28.6 (D2)
unnamed: Q28.2 (G1), U19.7 (OUT1)
unnamed: Q28.4 (G2), U19.5 (OUT2)
unnamed: Q28.1 (S1), Q29.1 (S1), R99.2, U18.17 (CS+)
unnamed: L8.2, Q29.5 (D1), Q29.6 (D2)
unnamed: Q29.2 (G1), U20.7 (OUT1)
unnamed: Q29.4 (G2), U20.5 (OUT2)
unnamed: R32.1, R33.2, U9.2 (-IN)
unnamed: C38.2, R38.2, R40.2, U9.6 (RG)
unnamed: C38.1, R38.1, U9.7 (OUT), U10.1 (CNTRL)
unnamed: NT2.1, U10.16 (CS-)
unnamed: C49.1, U10.28 (CT)
unnamed: C40.2, R44.1, U10.2 (EAOUT)
unnamed: C40.1, R42.1, R44.2, U10.3 (FB)
unnamed: U10.19 (NDRVA), U12.1 (IN1)
unnamed: U10.23 (NDRVB), U11.1 (IN1)
unnamed: U10.18 (PDRVA), U11.3 (IN2)
unnamed: U10.24 (PDRVB), U12.3 (IN2)
unnamed: R46.1, U10.30 (PLLLPF)
unnamed: R47.1, U10.31 (RSLEW)
unnamed: R48.2, U10.29 (RT)
unnamed: C42.2, U10.6 (SS)
unnamed: R49.1, R50.2, U10.14 (TEC+)
unnamed: R51.1, R52.2, U10.13 (TEC-)
unnamed: C36.1, R34.1, U9.3 (+IN), U10.10 (VTHRM)
unnamed: C61.1, R57.1, U13.3 (+IN), U14.10 (VTHRM)
unnamed: R55.1, R56.2, U13.2 (-IN)
unnamed: C63.1, R61.1, U13.7 (OUT), U14.1 (CNTRL)
unnamed: C63.2, R61.2, R63.2, U13.6 (RG)
unnamed: NT3.1, U14.16 (CS-)
unnamed: C74.1, U14.28 (CT)
unnamed: C65.2, R67.1, U14.2 (EAOUT)
unnamed: C65.1, R65.1, R67.2, U14.3 (FB)
unnamed: U14.19 (NDRVA), U16.1 (IN1)
unnamed: U14.23 (NDRVB), U15.1 (IN1)
unnamed: U14.18 (PDRVA), U15.3 (IN2)
unnamed: U14.24 (PDRVB), U16.3 (IN2)
unnamed: R69.1, U14.30 (PLLLPF)
unnamed: R70.1, U14.31 (RSLEW)
unnamed: R71.2, U14.29 (RT)
unnamed: C67.2, U14.6 (SS)
unnamed: R72.1, R73.2, U14.14 (TEC+)
unnamed: R74.1, R75.2, U14.13 (TEC-)
unnamed: C86.1, R80.1, U17.3 (+IN), U18.10 (VTHRM)
unnamed: R78.1, R79.2, U17.2 (-IN)
unnamed: C88.1, R84.1, U17.7 (OUT), U18.1 (CNTRL)
unnamed: C88.2, R84.2, R86.2, U17.6 (RG)
unnamed: NT4.1, U18.16 (CS-)
unnamed: C99.1, U18.28 (CT)
unnamed: C90.2, R90.1, U18.2 (EAOUT)
unnamed: C90.1, R88.1, R90.2, U18.3 (FB)
unnamed: U18.19 (NDRVA), U20.1 (IN1)
unnamed: U18.23 (NDRVB), U19.1 (IN1)
unnamed: U18.18 (PDRVA), U19.3 (IN2)
unnamed: U18.24 (PDRVB), U20.3 (IN2)
unnamed: R92.1, U18.30 (PLLLPF)
unnamed: R93.1, U18.31 (RSLEW)
unnamed: R94.2, U18.29 (RT)
unnamed: C92.2, U18.6 (SS)
unnamed: R95.1, R96.2, U18.14 (TEC+)
unnamed: R97.1, R98.2, U18.13 (TEC-)

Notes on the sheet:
Gate Driver Bypass
COOL
HEAT
Status Indicators
FAULT

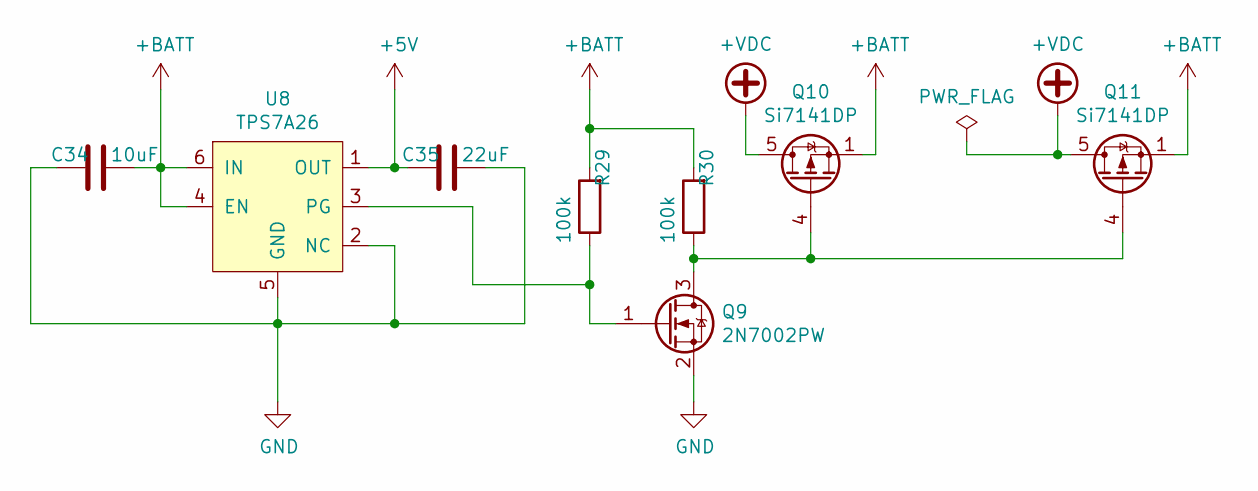
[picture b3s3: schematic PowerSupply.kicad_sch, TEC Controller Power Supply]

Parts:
C34: 10uF; C_0805_2012Metric; PartNo C2012X7S1E106K125AE
C35: 22uF; C_1206_3216Metric; PartNo 12063D226MAT2A
Q9: 2N7002PW; SOT-23; PartNo 2N7002PW,115
Q10, Q11: Si7141DP; PowerPAK_SO-8_Single; PartNo SI7141DP-T1-GE3
R29, R30: 100k; R_0805_2012Metric; PartNo RC0805FR-07100KL
U8: TPS7A26; WSON-6-1EP_2x2mm_P0.65mm_EP1x1.6mm_ThermalVias; PartNo TPS7A2650DRVR

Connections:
+5V: C35.2, U8.1 (OUT); also elsewhere on the board
+BATT: C34.1, Q10.1 (S), Q10.2 (S), Q10.3 (S), Q11.1 (S), Q11.2 (S), Q11.3 (S), R29.2, R30.2, U8.4 (EN), U8.6 (IN); also elsewhere on the board
+VDC: Q10.5 (D), Q11.5 (D); also elsewhere on the board
GND: C34.2, C35.1, Q9.2 (S), U8.2 (NC), U8.5 (GND), U8.7 (GND); also elsewhere on the board
unnamed: Q9.1 (G), R29.1, U8.3 (PG)
unnamed: Q9.3 (D), Q10.4 (G), Q11.4 (G), R30.1

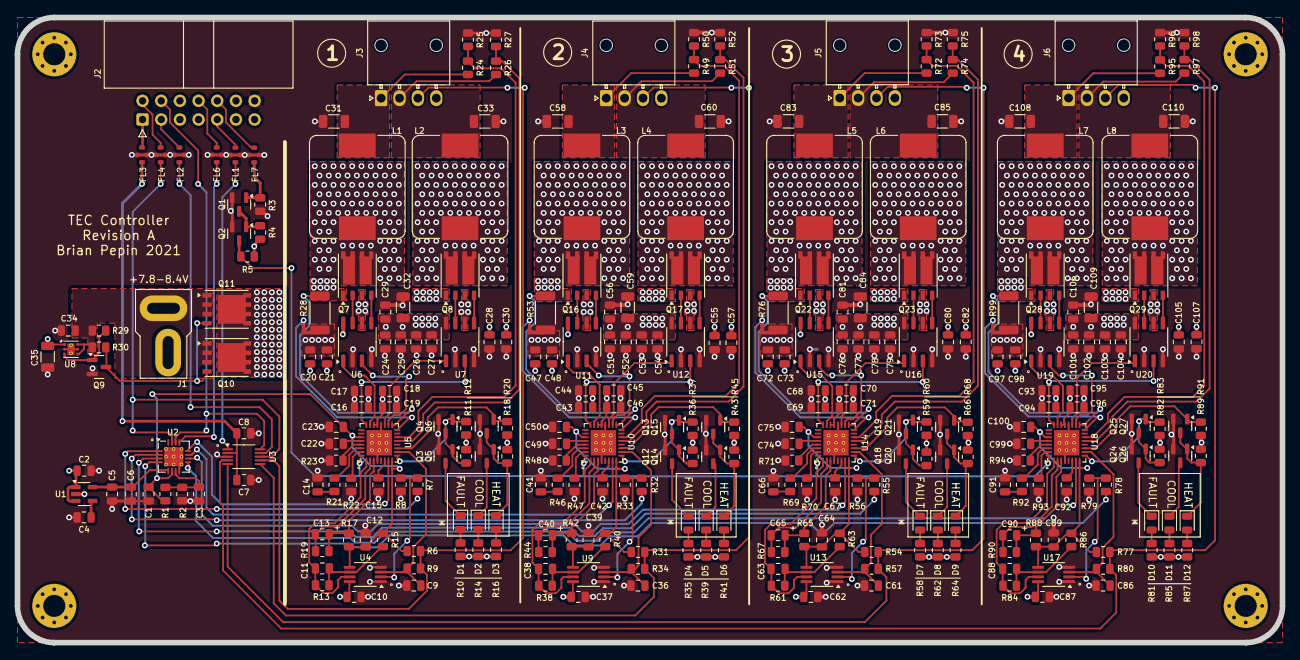
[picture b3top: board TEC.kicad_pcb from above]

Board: 4 copper layers, 172.0 x 85.0 mm, 298 parts (0 on the bottom side), 188 nets.
